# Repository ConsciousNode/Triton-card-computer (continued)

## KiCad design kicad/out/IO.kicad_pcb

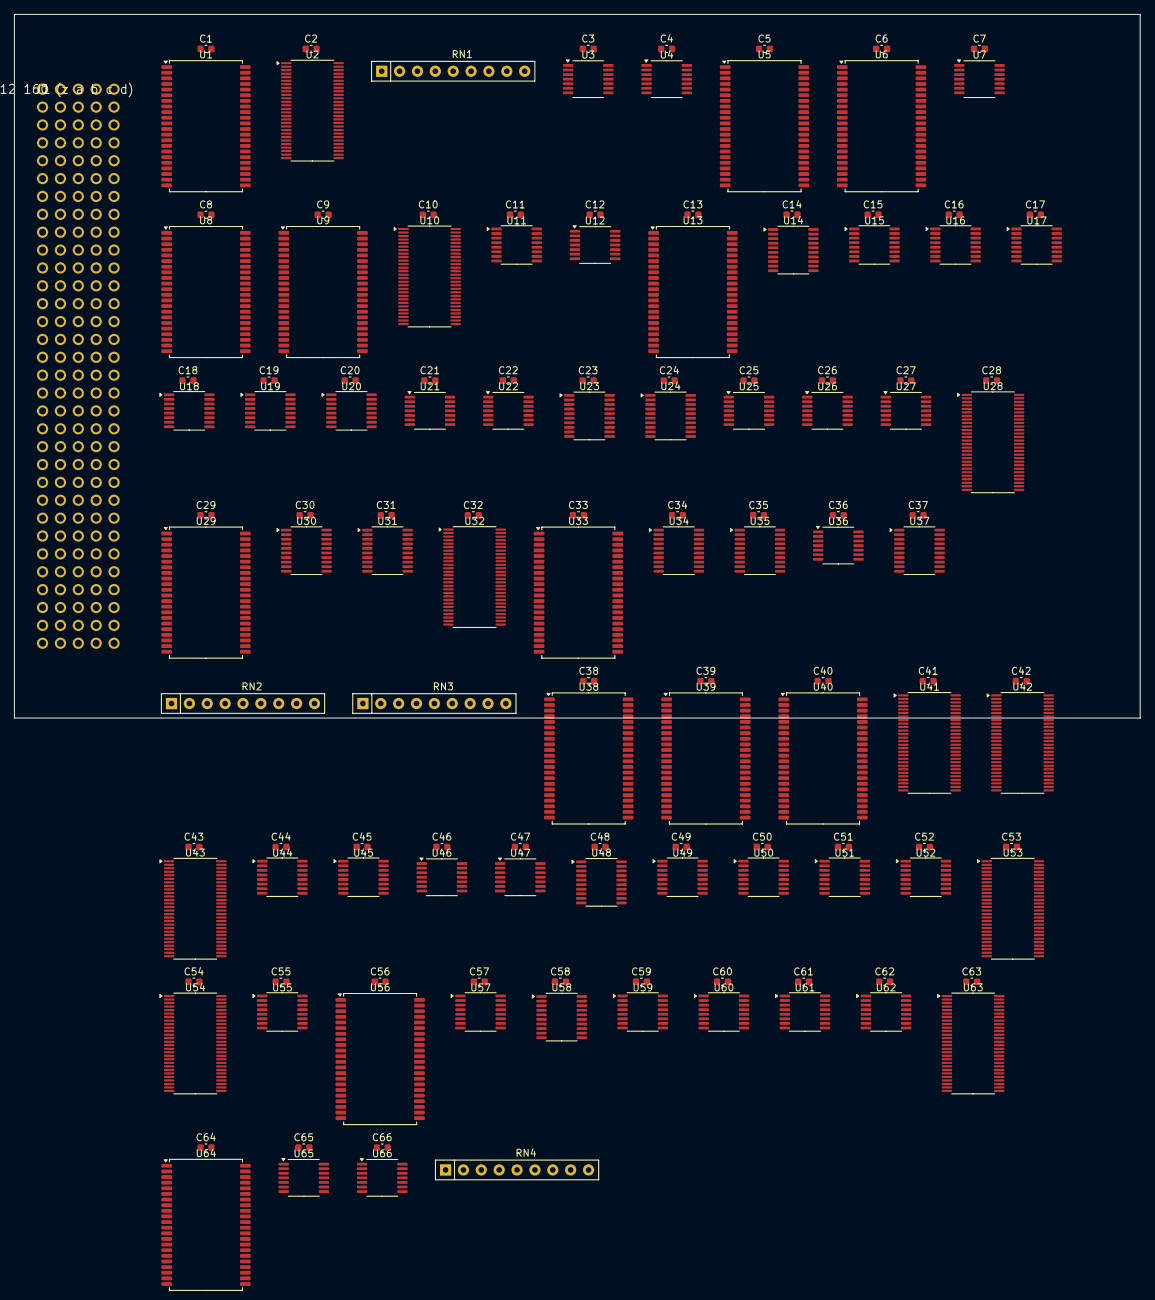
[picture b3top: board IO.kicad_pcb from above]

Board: 4 copper layers, 160.0 x 100.0 mm, 137 parts (0 on the bottom side), 346 nets, no tracks yet.

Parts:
C1, C2, C3, C4, C5, C6, C7, C8, C9, C10, C11, C12, C13, C14, C15, C16, C17, C18, C19, C20, C21, C22, C23, C24, C25, C26, C27, C28, C29, C30, C31, C32, C33, C34, C35, C36, C37, C38, C39, C40, C41, C42, C43, C44, C45, C46, C47, C48, C49, C50, C51, C52, C53, C54, C55, C56, C57, C58, C59, C60, C61, C62, C63, C64, C65, C66: 100n; C_0603_1608Metric
J1: DIN41612 160 (z a b c d)
RN1, RN2, RN3, RN4: RPACK8; R_Array_SIP9
U1, U5, U6, U13, U29, U33, U38, U39, U40, U56, U64: IS61WV5128; TSOP-II-44_10.16x18.41mm_P0.8mm
U2, U10, U28, U32, U41, U42, U43, U53, U54, U63: ALVCH16823; TSSOP-56_6.1x14mm_P0.5mm
U3: LVC04; TSSOP-14_4.4x5mm_P0.65mm
U4: LVC32; TSSOP-14_4.4x5mm_P0.65mm
U7, U12, U25, U26, U27, U46, U47, U65: LVC74; TSSOP-14_4.4x5mm_P0.65mm
U8, U9: IS61WV20488; TSOP-II-44_10.16x18.41mm_P0.8mm
U11: LVC157; TSSOP-16_4.4x5mm_P0.65mm
U14, U30, U31, U34, U35: LVC574; TSSOP-20_4.4x6.5mm_P0.65mm
U15, U16, U17, U18, U44, U45, U49, U50, U51, U52, U59, U60, U61, U62: LVC161; TSSOP-16_4.4x5mm_P0.65mm
U19, U20: LVC165; TSSOP-16_4.4x5mm_P0.65mm
U21, U22: LV164; TSSOP-14_4.4x5mm_P0.65mm
U23, U24, U37: LVC244; TSSOP-20_4.4x6.5mm_P0.65mm
U36: LVC125; TSSOP-14_4.4x5mm_P0.65mm
U48, U58: LV8154; TSSOP-20_4.4x6.5mm_P0.65mm
U55: LVC138; TSSOP-16_4.4x5mm_P0.65mm
U57: CD4060; TSSOP-16_4.4x5mm_P0.65mm
U66: LVC07; TSSOP-14_4.4x5mm_P0.65mm

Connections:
+3V3: C1.1, C2.1, C3.1, C4.1, C5.1, C6.1, C7.1, C8.1, C9.1, C10.1, C11.1, C12.1, C13.1, C14.1, C15.1, C16.1, C17.1, C18.1, C19.1, C20.1, C21.1, C22.1, C23.1, C24.1, C25.1, C26.1, C27.1, C28.1, C29.1, C30.1, C31.1, C32.1, C33.1, C34.1, C35.1, C36.1, C37.1, C38.1, C39.1, C40.1, C41.1, C42.1, C43.1, C44.1, C45.1, C46.1, C47.1, C48.1, C49.1, C50.1, C51.1, C52.1, C53.1, C54.1, C55.1, C56.1, C57.1, C58.1, C59.1, C60.1, C61.1, C62.1, C63.1, C64.1, C65.1, C66.1, J1.z2, J1.z4, J1.z6, J1.z10, J1.z12, J1.z14, J1.z18, J1.z20, J1.z22, J1.z26, J1.z28, J1.z30, RN1.1, RN2.1, RN3.1, RN4.1, U1.11, U1.15, U1.33, U2.1, U2.7, U2.22, U2.28, U2.35, U2.50, U3.14, U4.14, U5.11, U5.15, U5.33, U6.11, U6.15, U6.33, U7.4, U7.10, U7.14, U8.11, U8.15, U8.33, U9.11, U9.15, U9.33, U10.1, U10.7, U10.22, U10.28, U10.35, U10.50, U11.16, U12.4, U12.10, U12.13, U12.14, U13.11, U13.15, U13.33, U14.20, U15.1, U15.16, U16.1, U16.16, U17.1, U17.16, U18.1, U18.16, U19.16, U20.10, U20.16, U21.9, U21.14, U22.9, U22.14, U23.20, U24.20, U25.1, U25.4, U25.10, U25.13, U25.14, U26.1, U26.4, U26.10, U26.13, U26.14, U27.1, U27.4, U27.10, U27.13, U27.14, U28.7, U28.22, U28.35, U28.50, U29.11, U29.15, U29.33, U30.20, U31.20, U32.7, U32.22, U32.35, U32.50, U33.11, U33.15, U33.33, U34.20, U35.20, U36.10, U36.13, U36.14, U37.20, U38.11, U38.15, U38.33, U39.11, U39.15, U39.33, U40.11, U40.15, U40.33, U41.1, U41.7, U41.22, U41.28, U41.35, U41.50, U42.1, U42.7, U42.22, U42.28, U42.35, U42.50, U43.1, U43.7, U43.22, U43.28, U43.35, U43.50, U44.1, U44.6, U44.7, U44.10, U44.16, U45.1, U45.3, U45.4, U45.7, U45.16, U46.4, U46.10, U46.14, U47.4, U47.10, U47.14, U48.20, U49.16, U50.16, U51.16, U52.16, U53.7, U53.22, U53.35, U53.50, U54.7, U54.22, U54.30, U54.35, U54.50, U55.6, U55.16, U56.11, U56.15, U56.33, U57.16, U58.11, U58.20, U59.1, U59.3, U59.5, U59.7, U59.10, U59.16, U60.1, U60.4, U60.6, U60.7, U60.16, U61.1, U61.4, U61.5, U61.6, U61.7, U61.16, U62.3, U62.16, U63.7, U63.22, U63.30, U63.35, U63.50, U64.11, U64.15, U64.33, U65.1, U65.10, U65.13, U65.14, U66.5, U66.9, U66.11, U66.13, U66.14
+5V: J1.z8, J1.z16, J1.z24, J1.z32
/BLD: U59.9, U60.9, U61.9, U64.13
/BOE: U4.3, U41.2, U41.27, U42.2, U42.27, U43.2, U43.27
/CBUSY: U64.10, U66.3
/CEDGE: J1.c13, U5.19, U6.19, U29.39, U33.39, U56.19
/CSTART: U6.13, U62.9, U63.55, U64.29
/G0: U48.3, U55.15
/G1: U48.4, U55.14
/G2: U48.5, U55.13
/G3: U48.6, U55.12
/G4: U55.11, U58.3
/G5: U55.10, U58.4
/G6: U55.9, U58.5
/G7: U55.7, U58.6
/ISEL: U4.2, U7.6
/KB: U4.5, U25.8
/KC: U27.6, U28.54
/KCLR: U28.1, U28.28, U30.16
/KCLRD: U29.14, U30.5
/KRDY: U30.13, U36.1
/KRDYD: U29.35, U30.8
/KSH: U4.6, U28.30, U28.55
/LDANS: U5.13, U41.30, U41.55, U42.30, U42.55, U43.30, U43.55
/MB: U4.10, U26.8
/MC: U27.8, U32.54
/MCLR: U32.1, U32.28, U34.16
/MCLRD: U33.14, U34.5
/MRDY: U34.13, U36.4
/MRDYD: U33.35, U34.8
/MSH: U4.8, U32.30, U32.55
/OE_KD: U5.36, U31.1
/OE_MD: U6.9, U35.1
/OE_RX: U5.35, U23.1, U23.19, U24.1, U24.19
/OE_ST: U6.10, U37.1, U37.19
/OE_T: U55.4, U56.14
/PEPRE: U3.6, U44.9, U45.9
/PE_PER: U49.9, U50.9, U51.9, U52.9, U56.31
/PHLD: U13.31, U15.9, U16.9
/PRELD: U13.32, U17.9, U18.9
/RESET: U3.2, U7.1, U7.13, U12.1, U46.1, U46.13, U47.1, U47.13, U48.11, U49.1, U50.1, U51.1, U52.1, U53.1, U53.28, U54.1, U54.28, U62.1, U63.1, U63.28, U65.4
/SCK: U3.4, U19.2, U20.2
/START: U5.9, U10.30, U10.55, U13.38
/WRPH: U53.30, U56.10
/WRPL: U53.55, U56.9
/WRSEL: U54.55, U56.13
ANS0: RN2.2, U23.18, U31.19, U35.19, U37.18, U38.3, U39.3, U40.3, U48.19, U58.19
ANS1: RN2.3, U23.16, U31.18, U35.18, U37.16, U38.4, U39.4, U40.4, U48.18, U58.18
ANS2: RN2.4, U23.14, U31.17, U35.17, U37.14, U38.5, U39.5, U40.5, U48.17, U58.17
ANS3: RN2.5, U23.12, U31.16, U35.16, U37.12, U38.6, U39.6, U40.6, U48.16, U58.16
ANS4: RN2.6, U23.9, U31.15, U35.15, U37.9, U38.7, U39.7, U40.7, U48.15, U58.15
ANS5: RN2.7, U23.7, U31.14, U35.14, U37.7, U38.16, U39.16, U40.16, U48.14, U58.14
ANS6: RN2.8, U23.5, U31.13, U35.13, U37.5, U38.17, U39.17, U40.17, U48.13, U58.13
ANS7: RN2.9, U23.3, U31.12, U35.12, U37.3, U38.18, U39.18, U40.18, U48.12, U58.12
ANS8: RN3.2, U24.18, U38.19, U39.19, U40.19
ANS9: RN3.3, U24.16, U38.20, U39.20, U40.20
ANS10: RN3.4, U24.14, U38.26, U39.26, U40.26
ANS11: RN3.5, U24.12, U38.27, U39.27, U40.27
ANS12: RN3.6, U24.9, U38.28, U39.28, U40.28
ANS13: RN3.7, U24.7, U38.29, U39.29, U40.29
ANS14: RN3.8, U24.5, U38.30, U39.30, U40.30
ANS15: RN3.9, U24.3, U38.38, U39.38, U40.38
BT0: U38.9, U41.54
BT1: U38.10, U41.52
BT2: U38.13, U41.51
BT3: U38.14, U41.49
BT4: U38.31, U41.48
BT5: U38.32, U41.47
BT6: U38.35, U41.45
BT7: U38.36, U41.44
BT8: U39.9, U41.43
BT9: U39.10, U41.42
BT10: U39.13, U41.41
BT11: U39.14, U41.40
BT12: U39.31, U41.38
BT13: U39.32, U41.37
BT14: U39.35, U41.36
BT15: U39.36, U41.34
BT16: U40.9, U41.33
BT17: U40.10, U41.31
BT18: U40.13, U42.54
BT19: U40.14, U42.52
BT20: U40.31, U42.51
BT21: U40.32, U42.49
BTC: U61.15, U62.7, U64.28
BTC0: U59.15, U60.10
BTC1: U60.15, U61.10
BUSY: U13.28, U14.19
BUSYD: U13.9, U14.2
CB0: U62.14, U64.19
CB1: U62.13, U64.20
CB2: U62.12, U64.26
CB3: U62.11, U64.27
CBUSY: U62.10, U64.14
CLK: J1.c10, U2.29, U2.56
CS: U11.2, U12.5
CS0: U63.3, U64.3
CS1: U63.5, U64.4
CS2: U63.6, U64.5
CS3: U63.8, U64.6
CS4: U63.9, U64.7
CS5: U63.10, U64.16
CS6: U63.12, U64.17
CS7: U63.13, U64.18
CSD: U11.4, U12.2
CSD0: U1.9, U2.54
CSD1: U1.10, U2.52
CSD2: U1.13, U2.51
CW_/BIO: RN1.4, U2.6, U4.1
CW_/IN: RN1.2, U2.3, U5.17, U6.17, U56.17
CW_/OUT: RN1.3, U2.5, U5.18, U6.18, U56.18
D0+: J1.a1, U8.3, U9.3, U41.3
D0-: J1.a2, U8.4, U9.4, U41.5
D1+: J1.a3, U8.5, U9.5, U41.6
D1-: J1.a4, U8.6, U9.6, U41.8
D2+: J1.a5, U8.7, U9.7, U41.9
D2-: J1.a6, U8.16, U9.16, U41.10
D3+: J1.a7, U8.17, U9.17, U41.12
D3-: J1.a9, U8.18, U9.18, U41.13
D4+: J1.a10, U8.19, U9.19, U41.14
D4-: J1.a11, U8.20, U9.20, U41.15
D5+: J1.a12, U8.26, U9.26, U41.16
D5-: J1.a13, U8.27, U9.27, U41.17
D6+: J1.a14, U8.28, U9.28, U41.19
D6-: J1.a15, U8.29, U9.29, U41.20
D7+: J1.a17, U8.30, U9.30, U41.21
D7-: J1.a18, U8.38, U9.38, U41.23
D8+: J1.a19, U8.39, U9.39, U41.24
D8-: J1.a20, U8.40, U9.40, U41.26
D9+: J1.a21, U42.3
D9-: J1.a22, U42.5
D10+: J1.a23, U42.6
D10-: J1.a25, U42.8
D11+: J1.a26, U42.9
D11-: J1.a27, U42.10
D12+: J1.a28, U42.12
D12-: J1.a29, U42.13
D13+: J1.a30, U42.14
D13-: J1.a31, U42.15
D14+: J1.b1, U42.16
D14-: J1.b2, U42.17
D15+: J1.b3, U42.19
D15-: J1.b4, U42.20
D16+: J1.b5, U42.21
D16-: J1.b6, U42.23
D17+: J1.b7, U42.24
D17-: J1.b9, U42.26
D18+: J1.b10, U43.3
D18-: J1.b11, U43.5
D19+: J1.b12, U43.6
D19-: J1.b13, U43.8
D20+: J1.b14, U43.9
D20-: J1.b15, U43.10
D21+: J1.b17, U43.12
D21-: J1.b18, U43.13
D22+: J1.b19, U43.14
D22-: J1.b20, U43.15
D23+: J1.b21, U43.16
D23-: J1.b22, U43.17
D24+: J1.b23, U43.19
D24-: J1.b25, U43.20
D25+: J1.b26, U43.21
D25-: J1.b27, U43.23
D26+: J1.b28, U43.24
D26-: J1.b29, U43.26
FAST: U7.9, U11.5, U13.30
FASTD: U7.12, U11.7
GND: C1.2, C2.2, C3.2, C4.2, C5.2, C6.2, C7.2, C8.2, C9.2, C10.2, C11.2, C12.2, C13.2, C14.2, C15.2, C16.2, C17.2, C18.2, C19.2, C20.2, C21.2, C22.2, C23.2, C24.2, C25.2, C26.2, C27.2, C28.2, C29.2, C30.2, C31.2, C32.2, C33.2, C34.2, C35.2, C36.2, C37.2, C38.2, C39.2, C40.2, C41.2, C42.2, C43.2, C44.2, C45.2, C46.2, C47.2, C48.2, C49.2, C50.2, C51.2, C52.2, C53.2, C54.2, C55.2, C56.2, C57.2, C58.2, C59.2, C60.2, C61.2, C62.2, C63.2, C64.2, C65.2, C66.2, J1.a8, J1.a16, J1.a24, J1.a32, J1.b8, J1.b16, J1.b24, J1.b32, J1.c8, J1.c16, J1.c24, J1.c32, J1.d8, J1.d16, J1.d24, J1.d32, J1.z1, J1.z3, J1.z5, J1.z7, J1.z9, J1.z11, J1.z13, J1.z15, J1.z17, J1.z19, J1.z21, J1.z23, J1.z25, J1.z27, J1.z29, J1.z31, U1.8, U1.12, U1.26, U1.27, U1.28, U1.29, U1.30, U1.34, U1.37, U1.38, U1.39, U1.40, U1.41, U2.4, U2.11, U2.18, U2.25, U2.30, U2.31, U2.32, U2.33, U2.34, U2.36, U2.37, U2.38, U2.39, U2.40, U2.41, U2.42, U2.43, U2.44, U2.45, U2.46, U2.47, U2.48, U2.49, U2.53, U2.55, U3.7, U4.7, U5.8, U5.12, U5.26, U5.27, U5.28, U5.29, U5.30, U5.34, U5.37, U5.38, U5.39, U5.40, U5.41, U6.8, U6.12, U6.26, U6.27, U6.28, U6.29, U6.30, U6.34, U6.37, U6.38, U6.39, U6.40, U6.41, U7.7, U8.8, U8.12, U8.34, U8.37, U9.8, U9.12, U9.34, U9.37, U10.2, U10.4, U10.11, U10.18, U10.25, U10.27, U10.31, U10.32, U10.33, U10.39, U10.46, U10.53, U11.8, U11.10, U11.11, U11.13, U11.14, U11.15, U12.7, U12.11, U12.12, U13.8, U13.12, U13.34, U13.37, U13.41, U14.1, U14.6, U14.7, U14.8, U14.9, U14.10, U15.3, U15.4, U15.5, U15.6, U15.8, U16.3, U16.4, U16.5, U16.6, U16.8, U17.3, U17.4, U17.5, U17.6, U17.8, U18.3, U18.4, U18.5, U18.6, U18.8, U19.8, U19.15, U20.8, U20.15, U21.7, U22.7, U23.10, U24.10, U25.7, U26.7, U27.7, U28.2, U28.4, U28.11, U28.18, U28.25, U28.27, U28.31, U28.32, U28.33, U28.34, U28.36, U28.37, U28.38, U28.39, U28.40, U28.46, U28.53, U29.8, U29.12, U29.34, U29.37, U30.1, U30.9, U30.10, U31.10, U32.2, U32.4, U32.11, U32.18, U32.25, U32.27, U32.31, U32.32, U32.33, U32.34, U32.36, U32.37, U32.38, U32.39, U32.40, U32.46, U32.53, U33.8, U33.12, U33.34, U33.37, U34.1, U34.9, U34.10, U35.10, U36.2, U36.5, U36.7, U36.9, U36.12, U37.10, U37.17, U38.8, U38.12, U38.34, U38.37, U39.8, U39.12, U39.34, U39.37, U40.8, U40.12, U40.34, U40.37, U41.4, U41.11, U41.18, U41.25, U41.32, U41.39, U41.46, U41.53, U42.4, U42.11, U42.18, U42.25, U42.31, U42.32, U42.33, U42.34, U42.36, U42.37, U42.38, U42.39, U42.40, U42.41, U42.42, U42.43, U42.44, U42.45, U42.46, U42.47, U42.48, U42.53, U43.4, U43.11, U43.18, U43.25, U43.31, U43.32, U43.33, U43.34, U43.36, U43.37, U43.38, U43.39, U43.40, U43.41, U43.42, U43.43, U43.44, U43.45, U43.46, U43.47, U43.48, U43.49, U43.51, U43.52, U43.53, U43.54, U44.3, U44.4, U44.5, U44.8, U45.5, U45.6, U45.8, U46.7, U47.7, U48.10, U49.8, U50.8, U51.8, U52.8, U53.2, U53.4, U53.11, U53.18, U53.25, U53.27, U53.31, U53.32, U53.39, U53.43, U53.46, U53.53, U54.2, U54.4, U54.11, U54.18, U54.25, U54.27, U54.31, U54.32, U54.33, U54.34, U54.36, U54.37, U54.38, U54.39, U54.40, U54.41, U54.42, U54.43, U54.44, U54.45, U54.46, U54.47, U54.48, U54.53, U55.5, U55.8, U56.8, U56.12, U56.30, U56.34, U56.37, U56.38, U56.39, U56.40, U56.41, U57.8, U57.12, U58.10, U59.4, U59.6, U59.8, U60.3, U60.5, U60.8, U61.3, U61.8, U62.4, U62.5, U62.6, U62.8, U63.2, U63.4, U63.11, U63.18, U63.25, U63.27, U63.31, U63.32, U63.33, U63.34, U63.36, U63.37, U63.38, U63.39, U63.40, U63.41, U63.42, U63.43, U63.46, U63.53, U64.8, U64.12, U64.30, U64.34, U64.37, U64.38, U64.39, U64.40, U64.41, U65.7, U65.12, U66.7
IORDY: J1.d4, RN4.2, U66.2, U66.4
IRQ0D: U46.12, U56.32
IRQSET0: J1.d5, U46.9, U56.27
IRQSET1: J1.d6, U29.28, U30.18
IRQSET2: J1.d7, U33.28, U34.18
ISEL: U5.20, U6.20, U7.5
ISELD: U5.14, U7.2
KA: U4.4, U25.5, U25.12
KCAPD: U29.13, U30.4
KCAPQ: U29.29, U30.17, U31.11
KFERR: U29.41, U30.14, U37.8
KFERRD: U29.32, U30.7
KIRQD: U29.10, U30.3
KPERR: U29.40, U30.15, U37.6
KPERRD: U29.31, U30.6
KRDY: U29.27, U30.19, U37.4
KRDYD: U29.9, U30.2
KS0: U28.3, U28.52, U29.3
KS1: U28.5, U28.51, U29.4
KS2: U28.6, U28.49, U29.5, U31.9
KS3: U28.8, U28.48, U29.6, U31.8
KS4: U28.9, U28.47, U29.7, U31.7
KS5: U28.10, U28.45, U29.16, U31.6
KS6: U28.12, U28.44, U29.17, U31.5
KS7: U28.13, U28.43, U29.18, U31.4
KS8: U28.14, U28.42, U29.19, U31.3
KS9: U28.15, U28.41, U29.20, U31.2
KS10: U28.16, U29.26
MA: U4.9, U26.5, U26.12
MCAPD: U33.13, U34.4
MCAPQ: U33.29, U34.17, U35.11
MFERR: U33.41, U34.14, U37.15
MFERRD: U33.32, U34.7
MIRQD: U33.10, U34.3
MPERR: U33.40, U34.15, U37.13
MPERRD: U33.31, U34.6
MRDY: U33.27, U34.19, U37.11
MRDYD: U33.9, U34.2
MS0: U32.3, U32.52, U33.3
MS1: U32.5, U32.51, U33.4
MS2: U32.6, U32.49, U33.5, U35.9
MS3: U32.8, U32.48, U33.6, U35.8
MS4: U32.9, U32.47, U33.7, U35.7
MS5: U32.10, U32.45, U33.16, U35.6
MS6: U32.12, U32.44, U33.17, U35.5
MS7: U32.13, U32.43, U33.18, U35.4
MS8: U32.14, U32.42, U33.19, U35.3
MS9: U32.15, U32.41, U33.20, U35.2
MS10: U32.16, U33.26
N16: U13.29, U14.18
N16D: U13.10, U14.3
PH1: U13.18, U15.13
PH2: U13.19, U15.12
PH3: U13.20, U15.11
PH4: U13.26, U16.14
PH5: U13.27, U16.13
PHCE: U13.14, U15.7, U15.10, U16.7
PHTC: U15.15, U16.10
PORT0: J1.d17, U5.3, U6.3, U8.41, U9.41, U38.39, U39.39, U40.39, U56.3
PORT1: J1.d18, U5.4, U6.4, U8.25, U9.25, U13.39, U38.40, U39.40, U40.40, U56.4
PORT2: J1.d19, U5.5, U6.5, U8.42, U9.42, U38.41, U39.41, U40.41, U56.5
PORT3: J1.d20, U5.6, U6.6, U56.6
PORT4: J1.d21, U5.7, U6.7, U56.7
PORT5: J1.d22, U5.16, U6.16, U56.16
PRE0: U13.3, U17.14
PRE1: U13.4, U17.13
PRE2: U13.5, U17.12
PRE3: U13.6, U17.11
PRE4: U13.7, U18.14
PRE5: U13.16, U18.13
PRECE: U13.35, U17.7, U17.10, U18.7
PRETC: U17.15, U18.10
PTC0: U49.15, U50.10
PTC1: U50.15, U51.10
PTC2: U51.15, U52.10
QL: U19.10, U20.9
RCLKD: U47.12, U56.36
RCLKQ: U47.9, U48.7, U58.7
RDK: U5.31, U29.30
RDM: U5.32, U33.30
READYD: U13.36, U14.5
RESET: J1.c12, U2.2, U2.27, U3.1, U4.13, U13.40, U29.38, U33.38, U56.29
RTC_2HZ: U57.3, U58.1, U58.2
RX0: U21.3, U23.2
RX1: U21.4, U23.4
RX2: U21.5, U23.6
RX3: U21.6, U23.8
RX4: U21.10, U23.11
RX5: U21.11, U23.13
RX6: U21.12, U23.15
RX7: U21.13, U22.1, U22.2, U23.17
RX8: U22.3, U24.2
RX9: U22.4, U24.4
RX10: U22.5, U24.6
RX11: U22.6, U24.8
RX12: U22.10, U24.11
RX13: U22.11, U24.13
RX14: U22.12, U24.15
RX15: U22.13, U24.17
SCK: U3.3, U13.17, U15.14, U21.8, U22.8
SCLK: J1.c11, U7.3, U7.11, U10.29, U10.56, U12.3, U14.11, U15.2, U16.2, U17.2, U18.2, U25.3, U25.11, U26.3, U26.11, U27.3, U27.11, U28.29, U28.56, U30.11, U32.29, U32.56, U34.11, U41.29, U41.56, U42.29, U42.56, U43.29, U43.56, U44.2, U45.2, U46.3, U46.11, U47.3, U47.11, U49.2, U50.2, U51.2, U52.2, U53.29, U53.56, U54.29, U54.56, U59.2, U60.2, U61.2, U62.2, U63.29, U63.56, U65.3, U65.11
SD_MISO: U21.1, U21.2
SEL0: U54.3, U55.1
SEL1: U54.5, U55.2
SEL2: U54.6, U55.3
SH/LD: U14.17, U19.1, U20.1
SHLDD: U13.13, U14.4
SNAPP: U47.5, U56.28
SNAPPD: U47.2, U56.35
SREADY: U14.16, U66.1
TB0: U8.9, U10.54
TB1: U8.10, U10.52
TB2: U8.13, U10.51
TB3: U8.14, U10.49
TB4: U8.31, U10.48
TB5: U8.32, U10.47
TB6: U8.35, U10.45
TB7: U8.36, U10.44
TB8: U9.9, U10.43, U11.3, U53.42, U53.54, U54.54, U63.54
TB9: U9.10, U10.42, U11.6, U53.41, U53.52, U54.52, U63.52
TB10: U9.13, U10.41, U53.40, U53.51, U54.51, U63.51
TB11: U9.14, U10.40, U53.38, U53.49, U54.49, U63.49
TB12: U9.31, U10.38, U53.37, U53.48, U63.48
TB13: U9.32, U10.37, U53.36, U53.47, U63.47
TB14: U9.35, U10.36, U53.34, U53.45, U63.45
TB15: U9.36, U10.34, U53.33, U53.44, U63.44
TC4: U52.15, U56.20
TEN: U49.10, U54.8
TICK: U4.12, U45.15, U46.2, U49.7, U50.7, U51.7, U52.7, U56.26
TICKQ: U46.5, U48.1, U48.2
TPH0: U51.3, U53.15
TPH1: U51.4, U53.16
TPH2: U51.5, U53.17
TPH3: U51.6, U53.19
TPH4: U52.3, U53.20
TPH5: U52.4, U53.21
TPH6: U52.5, U53.23
TPH7: U52.6, U53.24
TPL0: U49.3, U53.3
TPL1: U49.4, U53.5
TPL2: U49.5, U53.6
TPL3: U49.6, U53.8
TPL4: U50.3, U53.9
TPL5: U50.4, U53.10
TPL6: U50.5, U53.12
TPL7: U50.6, U53.13
TPTC: U44.15, U45.10
TRST: U3.5, U4.11
TX0: U10.3, U20.11
TX1: U10.5, U20.12
TX2: U10.6, U20.13
TX3: U10.8, U20.14
TX4: U10.9, U20.3
TX5: U10.10, U20.4
TX6: U10.12, U20.5
TX7: U10.13, U20.6
TX8: U10.14, U19.11
TX9: U10.15, U19.12
TX10: U10.16, U19.13
TX11: U10.17, U19.14
TX12: U10.19, U19.3
TX13: U10.20, U19.4
TX14: U10.21, U19.5
TX15: U10.23, U19.6
TXD_D: U64.9, U65.2
U48_RCOA: U48.8, U48.9
U58_RCOA: U58.8, U58.9
UA0: J1.b30, U1.3
UA1: J1.b31, U1.4
UA2: J1.c1, U1.5
UA3: J1.c2, U1.6
UA4: J1.c3, U1.7
UA5: J1.c4, U1.16
UA6: J1.c5, U1.17
UA7: J1.c6, U1.18
UA8: J1.c7, U1.19
UA9: J1.c9, U1.20
WR41: U5.10, U11.1
